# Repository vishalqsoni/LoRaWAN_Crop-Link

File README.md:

# LoRaWAN_Crop-Link
Crop Link is a LoRa-based IoT data logging and communication system designed for reliable sensor data transmission from remote agricultural fields to the cloud Using LoRaWAN. The system operates independently of GSM or cellular networks.

Yes, this project is open source. The circuit contains some mistakes, as this is version 1.1.2, so please do not blindly follow the schematic. For detailed information and updates, please visit my Hackster page.
https://www.hackster.io/iwantmyspace2002/the-crop-link-25cf29

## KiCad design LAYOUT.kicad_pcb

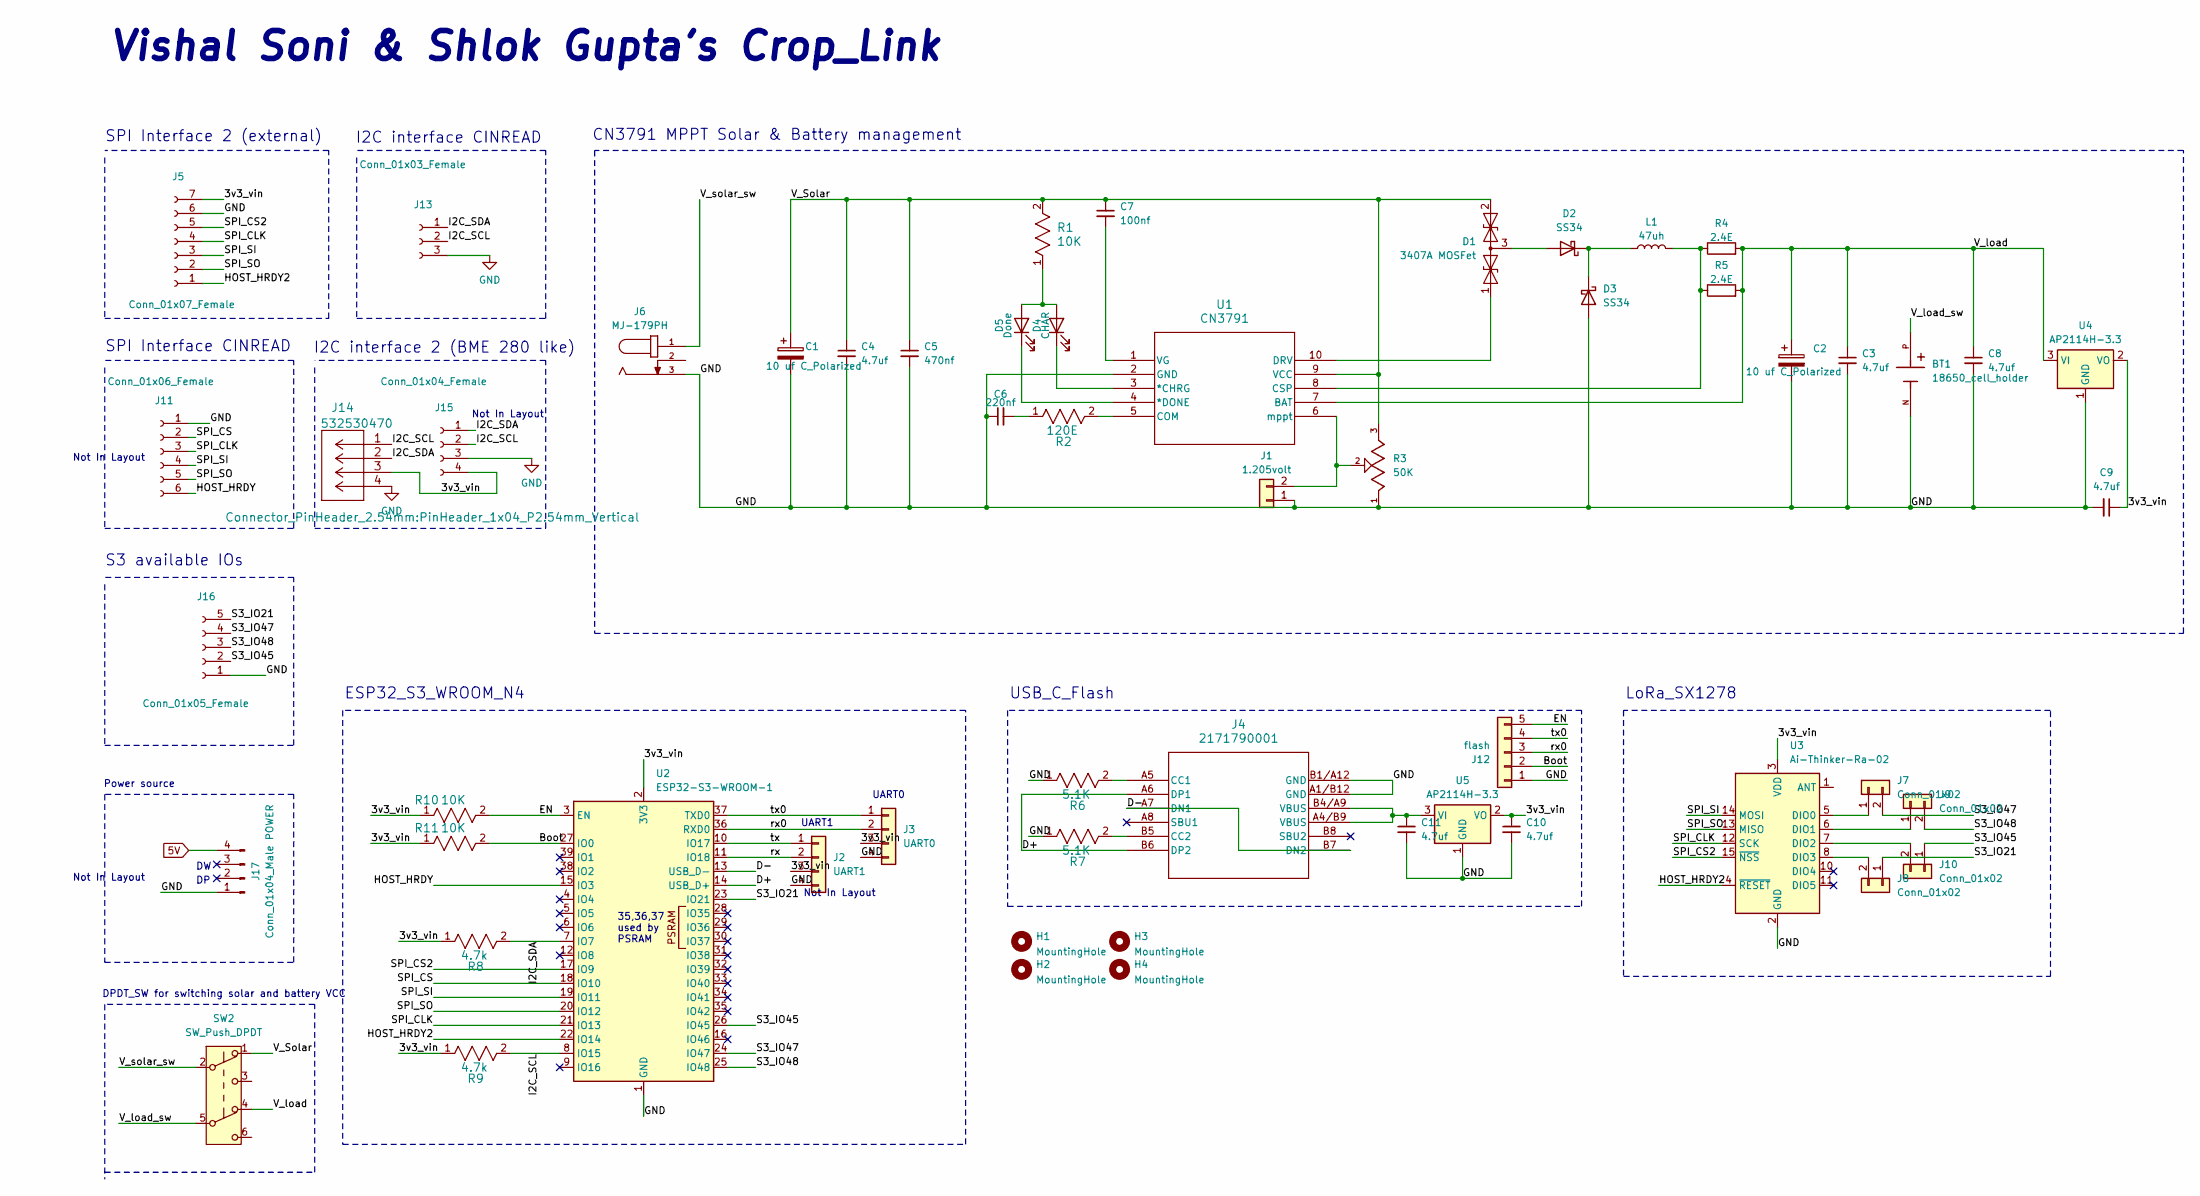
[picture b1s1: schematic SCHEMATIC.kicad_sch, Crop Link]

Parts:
BT1: 18650_cell_holder; PARTREV E
C1, C2: 10 uf C_Polarized; CP_Elec_4x5.4
C3, C4, C8, C9, C10, C11: 4.7uf; C_0603_1608Metric
C5: 470nf; C_0603_1608Metric
C6: 220nf; C_0603_1608Metric
C7: 100nf; C_0603_1608Metric
D1: 3407A MOSFet; SOT-23
D2, D3: SS34; D_SMA
D4: CHAR; LED_0603_1608Metric_Pad1.05x0.95mm_HandSolder
D5: Done; LED_0603_1608Metric_Pad1.05x0.95mm_HandSolder
H1, H2, H3, H4: MountingHole; MountingHole_2.5mm
J1: 1.205volt; PinHeader_1x02_P2.54mm_Vertical
J2: UART1; PinHeader_1x04_P2.54mm_Vertical
J3: UART0; PinHeader_1x04_P2.54mm_Vertical
J4: 2171790001; USB_C_Receptacle_GCT_USB4105-xx-A_16P_TopMnt_Horizontal
J5: Conn_01x07_Female; PinHeader_1x07_P2.54mm_Vertical
J6: MJ-179PH; 12Volt_Socket; VOLTAGE-RATING 12VDC; FARNELL 1737246
J7, J8, J9, J10: Conn_01x02; C_0201_0603Metric
J11: Conn_01x06_Female; PinHeader_1x06_P2.54mm_Vertical
J12: flash; PinHeader_1x05_P2.54mm_Vertical
J13: Conn_01x03_Female; PinHeader_1x03_P2.54mm_Vertical
J14: 532530470; PinHeader_1x04_P2.54mm_Vertical
J15: Conn_01x04_Female; PinHeader_1x04_P2.54mm_Vertical
J16: Conn_01x05_Female; PinHeader_1x05_P1.27mm_Vertical
J17: Conn_01x04_Male POWER; PinHeader_1x04_P2.54mm_Vertical
L1: 47uh; L_Coilcraft_MSS1210-XXX
R1, R10, R11: 10K; R_0603_1608Metric_Pad0.98x0.95mm_HandSolder
R2: 120E; R_0603_1608Metric_Pad0.98x0.95mm_HandSolder
R3: 50K; 50K_preset; PARTREV 08/19
R4, R5: 2.4E; R_Axial_DIN0204_L3.6mm_D1.6mm_P5.08mm_Horizontal
R6, R7: 5.1K; R_0603_1608Metric_Pad0.98x0.95mm_HandSolder
R8, R9: 4.7k; R_0603_1608Metric_Pad0.98x0.95mm_HandSolder
SW2: SW_Push_DPDT; DPDT_switch_angled
U1: CN3791; cn3763A
U2: ESP32-S3-WROOM-1
U3: Ai-Thinker-Ra-02; Ai-Thinker-Ra-01-LoRa
U4, U5: AP2114H-3.3; SOT-223-3_TabPin2

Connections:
/3v3_vin: C9.1, C10.1, J2.3, J3.3, J5.7, J14.3, J15.4, R8.1, R9.1, R10.1, R11.1, U2.2 (3V3), U3.3 (VDD), U4.2 (VO), U5.2 (VO)
/Boot: J12.2, R11.2, U2.27 (IO0)
/D+: J4.A6 (DP1), J4.B6 (DP2), U2.14 (USB_D+)
/D-: J4.A7 (DN1), J4.B7 (DN2), U2.13 (USB_D-)
/EN: J12.5, R10.2, U2.3 (EN)
/HOST_HRDY: J11.6, U2.15 (IO3)
/HOST_HRDY2: J5.1, U2.22 (IO14), U3.4 (~RESET)
/I2C_SCL: J13.2, J14.1, J15.2, R9.2, U2.8 (IO15)
/I2C_SDA: J13.1, J14.2, J15.1, R8.2, U2.7 (IO7)
/S3_IO21: J8.1, J16.5, U2.23 (IO21)
/S3_IO45: J10.1, J16.2, U2.26 (IO45)
/S3_IO47: J7.2, J16.4, U2.24 (IO47)
/S3_IO48: J9.2, J16.3, U2.25 (IO48)
/SPI_CLK: J5.4, J11.3, U2.21 (IO13), U3.12 (SCK)
/SPI_CS: J11.2, U2.18 (IO10)
/SPI_CS2: J5.5, U2.17 (IO9), U3.15 (~NSS)
/SPI_SI: J5.3, J11.4, U2.19 (IO11), U3.14 (MOSI)
/SPI_SO: J5.2, J11.5, U2.20 (IO12), U3.13 (MISO)
/V_Solar: C1.1, C4.1, C5.1, C7.1, D1.2 (A2), R1.2, R3.3, SW2.1 (A), U1.9 (VCC)
/V_load_sw: BT1.P, SW2.5 (B)
/V_solar_sw: J6.1, SW2.2 (B)
/rx: J2.2, U2.11 (IO18)
/rx0: J3.2, J12.3, U2.36 (RXD0)
/tx: J2.1, U2.10 (IO17)
/tx0: J3.1, J12.4, U2.37 (TXD0)
unnamed: C6.2, R2.1
unnamed: D1.1 (A1), U1.10 (DRV)
unnamed: D1.3 (common), D2.2 (A)
unnamed: D2.1 (K), D3.1 (K), L1.1
unnamed: D4.2 (A), D5.2 (A), R1.1
unnamed: D4.1 (K), U1.3 (*CHRG)
unnamed: D5.1 (K), U1.4 (*DONE)
unnamed: J1.2, R3.2, U1.6 (mppt)
unnamed: J4.A5 (CC1), R6.2
unnamed: J4.B5 (CC2), R7.2
unnamed: J7.1, U3.5 (DIO0)
unnamed: J8.2, U3.8 (DIO3)
unnamed: J9.1, U3.6 (DIO1)
unnamed: J10.2, U3.7 (DIO2)
unnamed: R2.2, U1.5 (COM)
unnamed: L1.2, R4.1, R5.1, U1.8 (CSP)
unnamed: C7.2, U1.1 (VG)
unnamed: C11.1, J4.A4/B9 (VBUS), J4.B4/A9 (VBUS), U5.3 (VI)

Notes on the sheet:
UART0
ESP32_S3_WROOM_N4
USB_C_Flash
35,36,37 used by PSRAM
Not In Layout
S3 available IOs
Power source
SPI Interface CINREAD
Vishal Soni & Shlok Gupta's Crop_Link
CN3791 MPPT Solar & Battery management
UART1
SPI Interface 2 (external)
DPDT_SW for switching solar and battery VCC
I2C interface 2 (BME 280 like)
LoRa_SX1278
I2C interface CINREAD

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
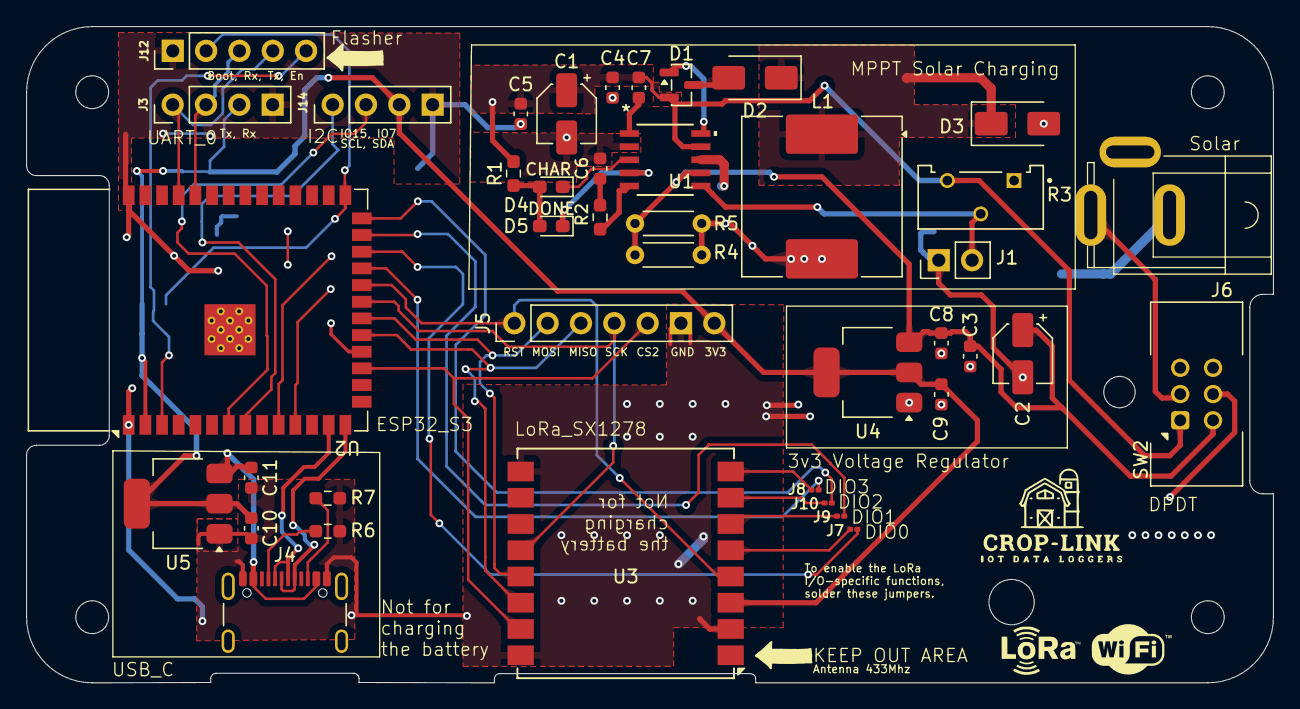
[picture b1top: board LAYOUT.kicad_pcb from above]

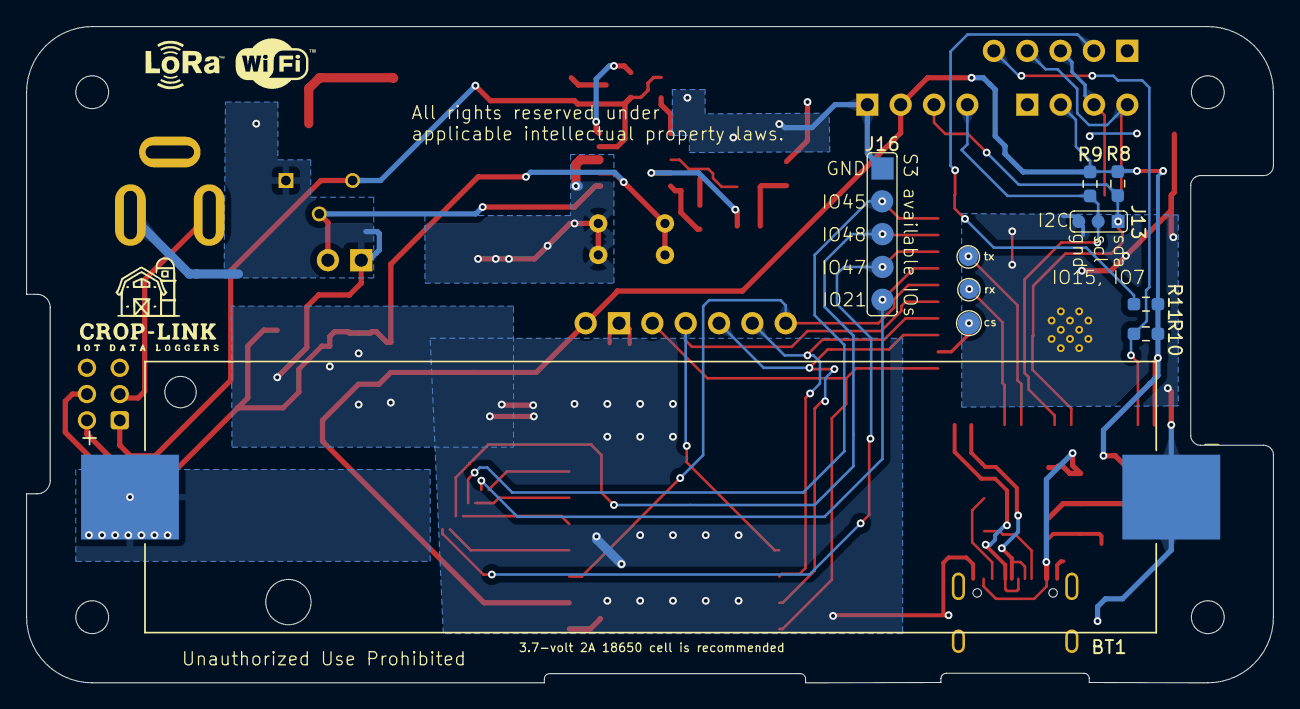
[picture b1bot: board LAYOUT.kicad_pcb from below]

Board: 2 copper layers, 95.0 x 50.0 mm, 52 parts (7 on the bottom side), 41 nets.

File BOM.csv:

"Reference","Qty","Value","DNP","Exclude from BOM","Exclude from Board","Footprint","Datasheet"
"BT1","1","18650_cell_holder","","","","LoRa_Link:18650_cell_holder",""
"C1,C2","2","10 uf C_Polarized","","","","Capacitor_SMD:CP_Elec_4x5.4","~"
"C3,C4,C8,C9,C10,C11","6","4.7uf","","","","Capacitor_SMD:C_0603_1608Metric","~"
"C5","1","470nf","","","","Capacitor_SMD:C_0603_1608Metric","~"
"C6","1","220nf","","","","Capacitor_SMD:C_0603_1608Metric","~"
"C7","1","100nf","","","","Capacitor_SMD:C_0603_1608Metric","~"
"D1","1","3407A MOSFet","","","","Package_TO_SOT_SMD:SOT-23","https://www.littelfuse.com/~/media/electronics/datasheets/tv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"
"D2,D3","2","SS34","","","","Diode_SMD:D_SMA","https://www.vishay.com/docs/88751/ss32.pdf"
"D4","1","CHAR","","","","LED_SMD:LED_0603_1608Metric_Pad1.05x0.95mm_HandSolder","~"
"D5","1","Done","","","","LED_SMD:LED_0603_1608Metric_Pad1.05x0.95mm_HandSolder","~"
"H1,H2,H3,H4","4","MountingHole","","","","MountingHole:MountingHole_2.5mm","~"
"J1","1","1.205volt","","","","Connector_PinHeader_2.54mm:PinHeader_1x02_P2.54mm_Vertical","~"
"J2","1","UART1","","","","Connector_PinHeader_2.54mm:PinHeader_1x04_P2.54mm_Vertical","~"
"J3","1","UART0","","","","Connector_PinHeader_2.54mm:PinHeader_1x04_P2.54mm_Vertical","~"
"J4","1","2171790001","","","","Connector_USB:USB_C_Receptacle_GCT_USB4105-xx-A_16P_TopMnt_Horizontal","https://www.molex.com/en-us/products/part-detail-pdf/2171790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"
"J5","1","Conn_01x07_Female","","","","Connector_PinHeader_2.54mm:PinHeader_1x07_P2.54mm_Vertical","~"
"J6","1","MJ-179PH","","","","LoRa_Link:12Volt_Socket",""
"J7,J8,J9,J10","4","Conn_01x02","","","","Capacitor_SMD:C_0201_0603Metric","~"
"J11","1","Conn_01x06_Female","","","","Connector_PinHeader_2.54mm:PinHeader_1x06_P2.54mm_Vertical","~"
"J12","1","flash","","","","Connector_PinHeader_2.54mm:PinHeader_1x05_P2.54mm_Vertical","~"
"J13","1","Conn_01x03_Female","","","","Connector_PinHeader_2.54mm:PinHeader_1x03_P2.54mm_Vertical","~"
"J14","1","532530470","","","","Connector_PinHeader_2.54mm:PinHeader_1x04_P2.54mm_Vertical",""
"J15","1","Conn_01x04_Female","","","","Connector_PinHeader_2.54mm:PinHeader_1x04_P2.54mm_Vertical","~"
"J16","1","Conn_01x05_Female","","","","Connector_PinHeader_1.27mm:PinHeader_1x05_P1.27mm_Vertical","~"
"J17","1","Conn_01x04_Male POWER","","","","Connector_PinHeader_2.54mm:PinHeader_1x04_P2.54mm_Vertical","~"
"L1","1","47uh","","","","Inductor_SMD:L_Coilcraft_MSS1210-XXX","~"
"R1,R10,R11","3","10K","","","","Resistor_SMD:R_0603_1608Metric_Pad0.98x0.95mm_HandSolder","ERJPA3F1803V"
"R2","1","120E","","","","Resistor_SMD:R_0603_1608Metric_Pad0.98x0.95mm_HandSolder","ERJPA3F1803V"
"R3","1","50K","","","","LoRa_Link:50K_preset",""
"R4,R5","2","2.4E","","","","Resistor_THT:R_Axial_DIN0204_L3.6mm_D1.6mm_P5.08mm_Horizontal","~"
"R6,R7","2","5.1K","","","","Resistor_SMD:R_0603_1608Metric_Pad0.98x0.95mm_HandSolder","ERJPA3F1803V"
"R8,R9","2","4.7k","","","","Resistor_SMD:R_0603_1608Metric_Pad0.98x0.95mm_HandSolder","ERJPA3F1803V"
"SW2","1","SW_Push_DPDT","","","","Button_Switch_THT:DPDT_switch_angled","~"
"U1","1","CN3791","","","","LoRa_Link:cn3763A","CN3763"
"U2","1","ESP32-S3-WROOM-1","","","","RF_Module:ESP32-S3-WROOM-1","https://www.espressif.com/sites/default/files/documentation/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"
"U3","1","Ai-Thinker-Ra-02","","","","RF_Module:Ai-Thinker-Ra-01-LoRa","http://wiki.ai-thinker.com/_media/lora/docs/c047ps01a1_ra-01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"
"U4,U5","2","AP2114H-3.3","","","","Package_TO_SOT_SMD:SOT-223-3_TabPin2","http://www.advanced-monolithic.com/pdf/ds1117.pdf"

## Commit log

2026-01-18 Initial plan
2026-01-18 Rename project files with numerical prefixes for proper ordering

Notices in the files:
LAYOUT.kicad_pcb:
All rights reserved under
applicable intellectual property laws.
